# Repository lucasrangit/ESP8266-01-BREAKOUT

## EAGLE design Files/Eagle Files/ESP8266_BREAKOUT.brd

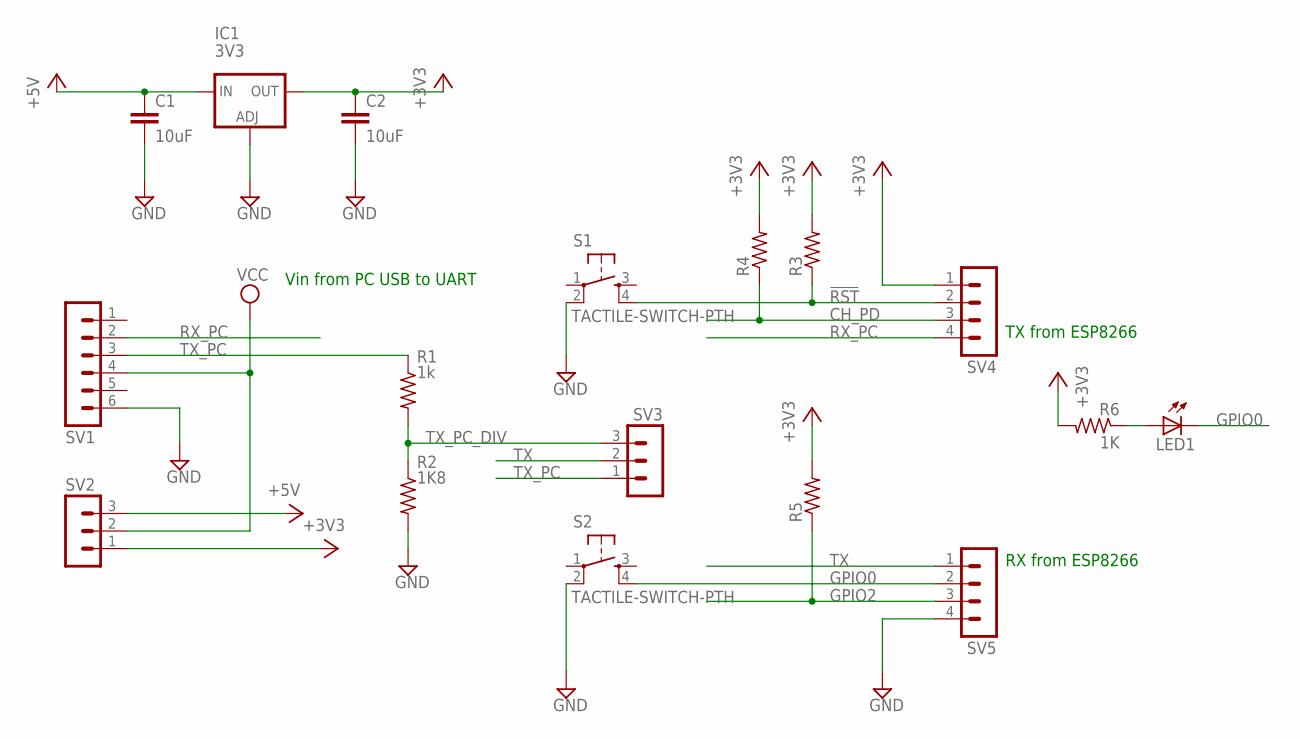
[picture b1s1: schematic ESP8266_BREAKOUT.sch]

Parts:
C1, C2: 10uF; C5B2.5
IC1: 3V3; 317TS
LED1: LED5MM
R1: 1k; 0204/7
R2: 1K8; 0204/7
R3, R4, R5: R-US_0204/7; 0204/7
R6: 1K; 0204/7
S1, S2: TACTILE-SWITCH-PTH; TAC-SWITCH-PTH
SV1: MA06-1
SV2, SV3: MA03-1
SV4, SV5: MA04-1

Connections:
!RST: R3.1, S1.4, SV4.2
+3V3: C2.1, IC1.2 (OUT), R3.2, R4.2, R5.2, R6.2, SV2.1, SV4.1
+5V: C1.1, IC1.3 (IN), SV2.3
CH_PD: R4.1, SV4.3
GND: C1.2, C2.2, IC1.1 (ADJ), R2.2, S1.2, S2.2, SV1.6, SV5.4
GPIO0: LED1.K (C), S2.4, SV5.2
GPIO2: R5.1, SV5.3
unnamed: LED1.A, R6.1
RX_PC: SV1.2, SV4.4
TX: SV3.2, SV5.1
TX_PC: R1.1, SV1.3, SV3.1
TX_PC_DIV: R1.2, R2.1, SV3.3
VCC: SV1.4, SV2.2

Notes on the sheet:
TX from ESP8266
RX from ESP8266
Vin from PC USB to UART

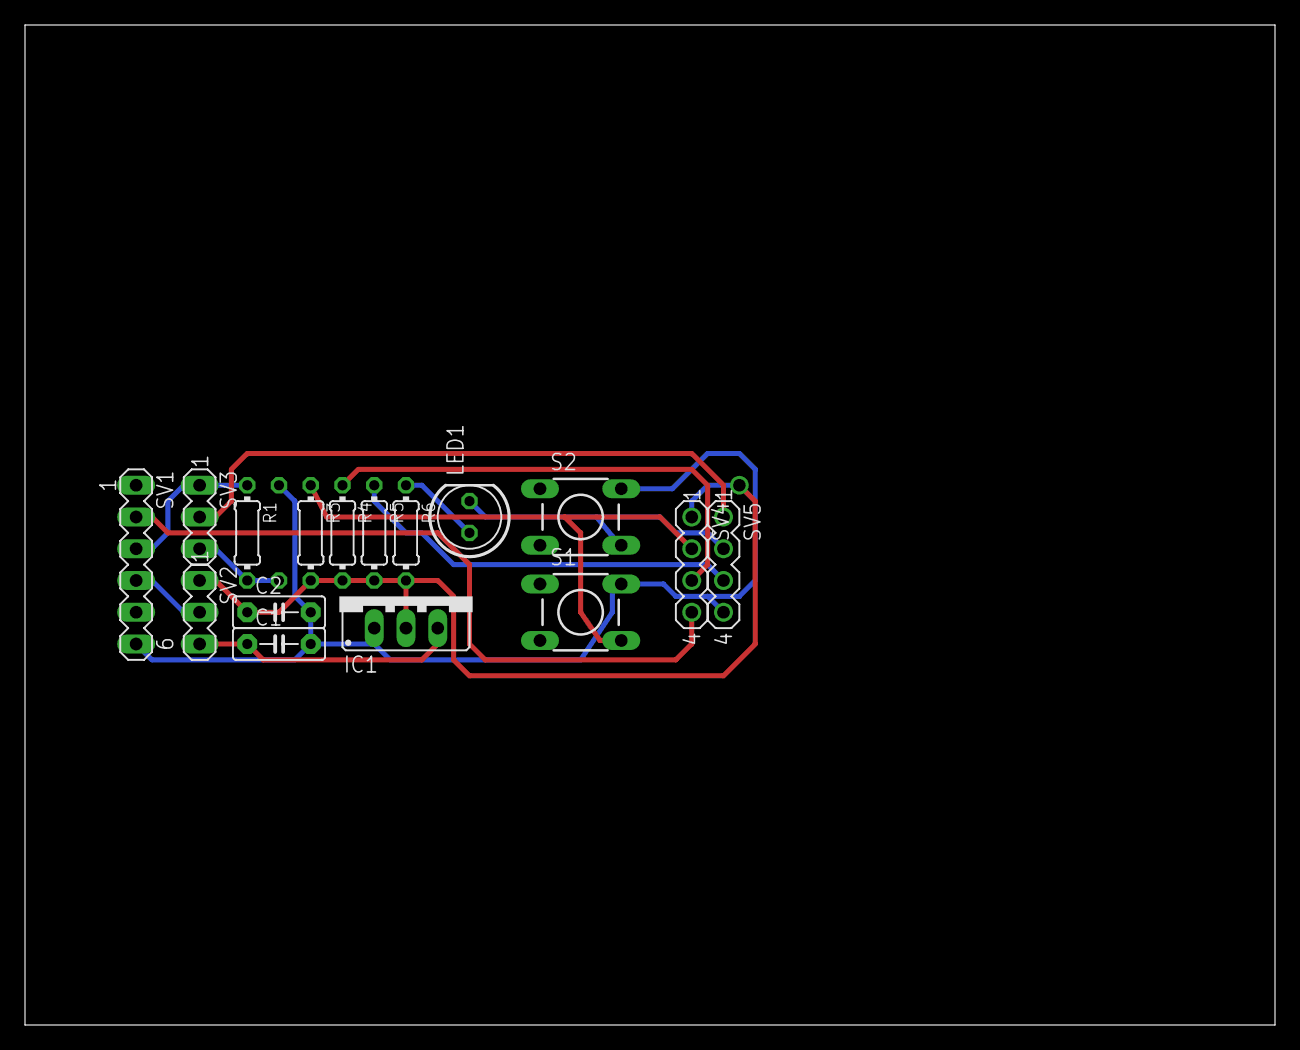
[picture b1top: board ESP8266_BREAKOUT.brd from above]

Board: 2 copper layers, 100.0 x 80.0 mm, 17 parts (1 on the bottom side), 13 nets.

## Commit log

2015-05-13 My implementation of the ESP8266-01 breakout board
2015-05-13 Picture of board layout.

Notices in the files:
parts and their libraries:
GeekAmmo: Licensing:Creative Commons ShareAlike 4.0 International - https://creativecommons.org/licenses/by-sa/4.0
